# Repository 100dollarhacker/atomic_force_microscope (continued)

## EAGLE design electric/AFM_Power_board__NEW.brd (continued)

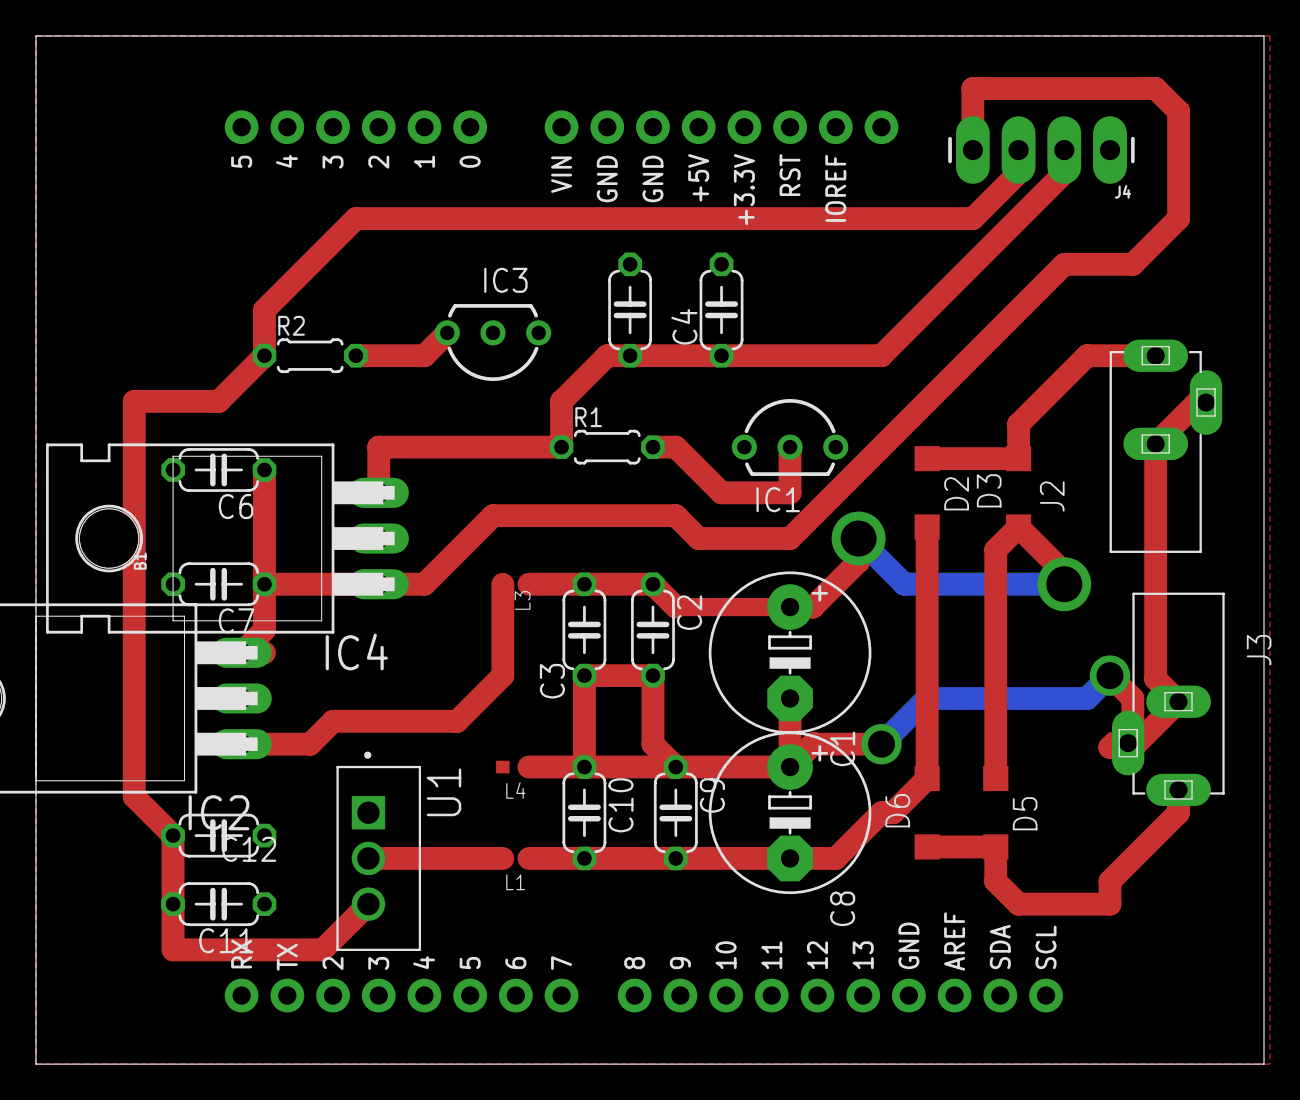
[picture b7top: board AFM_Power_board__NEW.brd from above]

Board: 2 copper layers, 68.2 x 57.1 mm, 30 parts (0 on the bottom side), 13 nets.

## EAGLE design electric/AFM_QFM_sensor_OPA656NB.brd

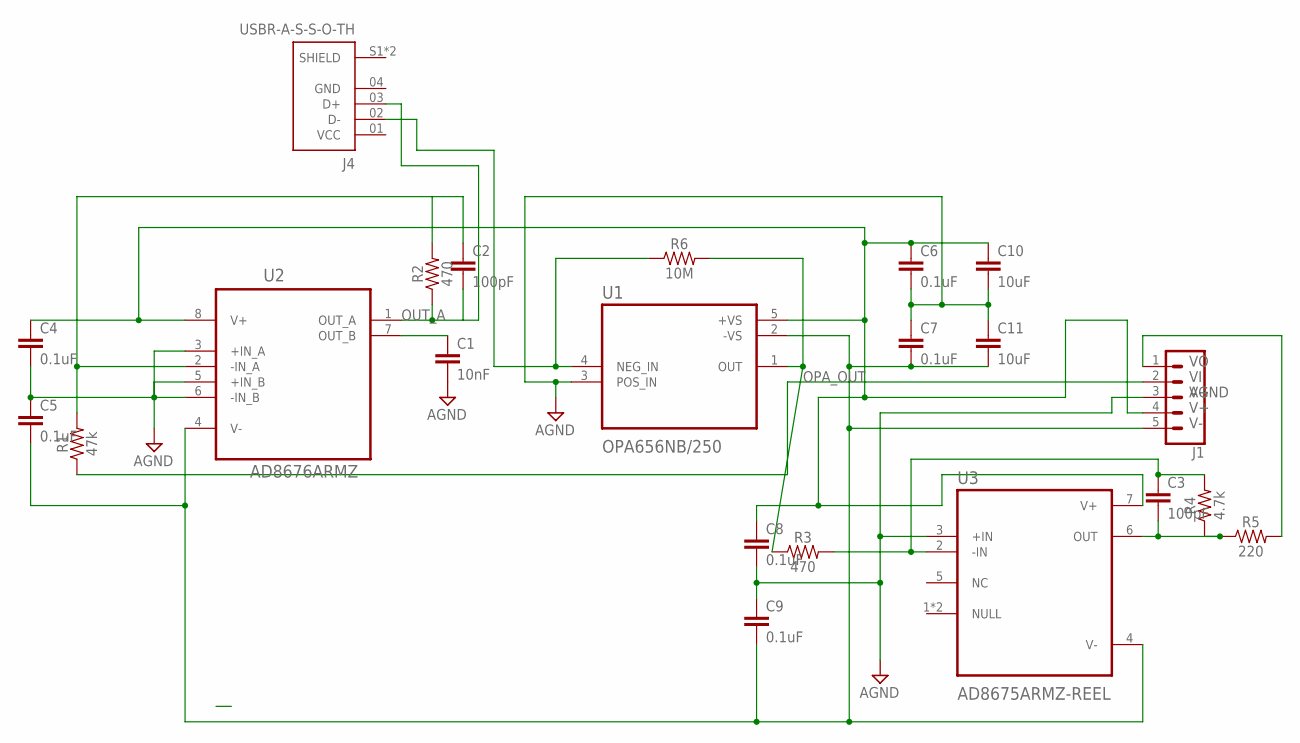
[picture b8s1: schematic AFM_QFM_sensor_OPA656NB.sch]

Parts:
C1: 10nF; 0603
C2, C3: 100pF; 0603
C4, C5, C6, C7, C8, C9: 0.1uF; 0603
C10, C11: 10uF; 0805
J1: CONN_05PTH_LONGPADS; 1X05_LONGPADS
J4: USBR-A-S-S-O-TH; SAMTEC_USBR-A-S-S-O-TH
R1: 47k; 0603
R2, R3: 470; 0603
R4: 4.7k; 0603
R5: 220; 0603
R6: 10M; 0603
U1: OPA656NB/250; SOT95P280X145-5N
U2: AD8676ARMZ; SOP65P490X110-8N
U3: AD8675ARMZ-REEL; SOP65P490X110-8N

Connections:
AGND: C1.2, C4.2, C5.1, C6.2, C7.1, C8.2, C9.1, C10.2, C11.1, J1.3, U1.3 (POS_IN), U2.3 (+IN_A), U2.5 (+IN_B), U2.6 (-IN_B), U3.3 (+IN)
GND: J4.04 (GND)
unnamed: J4.02 (D-), R6.1, U1.4 (NEG_IN)
unnamed: C1.1, U2.7 (OUT_B)
unnamed: C2.1, R1.2, R2.2, U2.2 (-IN_A)
unnamed: C3.2, R4.1, R5.1, U3.6 (OUT)
OPA_OUT: C3.1, R3.1, R3.2, R4.2, R6.2, U1.1 (OUT), U3.2 (-IN)
OUT_A: C2.2, J4.03 (D+), R2.1, U2.1 (OUT_A)
V+: C4.1, C6.1, C8.1, C10.1, J1.4, U1.5 (+VS), U2.8 (V+), U3.7 (V+)
V-: C5.2, C7.2, C9.2, C11.2, J1.5, U1.2 (-VS), U2.4 (V-), U3.4 (V-)
VCC: J4.01 (VCC)
VI: J1.2, R1.1
VO: J1.1, R5.2

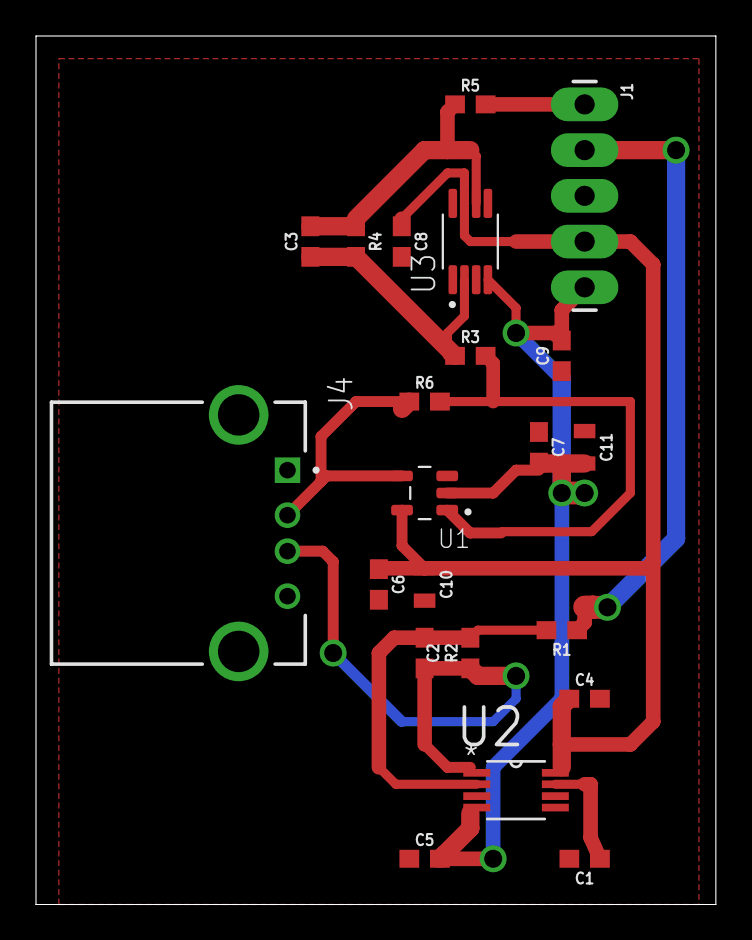
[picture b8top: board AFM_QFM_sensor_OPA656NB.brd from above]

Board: 2 copper layers, 37.8 x 48.2 mm, 22 parts (0 on the bottom side), 11 nets.

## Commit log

2023-07-18 Files needed to create nono sized tip
2023-07-21 old OpenAFM schematics
2023-08-17 This is a very basic but working DAC
2023-10-08 POC fine mechanical and coarse mechanical
2023-10-12 Nano probe holder
2024-03-05 initial electoring circuits added
2024-04-05 allboards
2024-04-06 movied power lines to right position
2024-05-19 Charge pump with his own power source
2024-07-04 new firmware
2024-07-05 UI and simple main components
2024-07-06 more components
2024-07-07 Connected AD5696 conroll
2024-07-07 swing in Z working
2024-07-07 some last minute fixs
2024-07-08 ad9833 controller
2024-07-08 Added frequency sensor
2024-07-09 working my code
2024-08-04 afm sensor holder with bolts holders
2024-08-04 upper parth with bolt holder
2024-08-17 new functions and samples
2024-11-04 newer electroincs
2024-12-21 use long as int is 16bit
2024-12-21 simplfy freq
2024-12-22 minor fix
2024-12-30 software change, try to run with one frequncy
2024-12-30 BOM - Bill Of Materials for all the boards
2024-12-30 Updated to boards. Changes reflects fixes needed to PCBWay boards
2024-12-30 removed unused files
2024-12-30 removed old
2024-12-30 remove old files
2025-02-27 different kind of scans
2025-02-27 first data visualized
2025-03-07 added ringing functionality to check piezos and added micropositioner controller
2025-03-19 simple gui added, mainly buttons that doesn't do a thing and a plot with fake data
2025-03-19 colorbar added
2025-03-20 frequency controll added
2025-03-21 serial connected, getting/setting freq done
2025-03-21 send the min freuency
2025-03-21 added scan thread and other buttons
2025-03-21 added lr and rl scans
2025-03-22 most of the buttons are functional, not tested on real device yet
2025-03-23 made most of function to work with GUI
2025-03-23 make GUI work with firmaware mostly
2025-03-24 get the data
2025-03-24 up/down firmware
2025-03-26 make it run faster
2025-03-26 different maginfications
2025-05-20 make serail a thread
2025-05-20 range with number
2025-05-20 made posible to run scan prallel to down/up
2025-05-20 demo flag added
2025-05-23 adding ability to trace surface
2025-05-23 still debuging
2025-05-23 some silly debugs
2025-05-24 fix merge
2025-05-25 strange build behavior
2025-05-26 fixed scanxlr
2025-05-26 scanning looks good
2025-05-27 moving to more efficient serial reader implementation
2025-05-27 simiplified serial communications
2025-05-27 working now
2025-09-25 make range work again
2025-09-26 wrong merge
2025-09-26 frequency are not limited by 32768
2025-09-26 removing tiny bug which made me a lot of troubles
2025-09-26 typo
2025-10-04 tested version of approach
2025-10-10 remove debugs so scannig could work nwo
2025-10-11 name changed and fixed direction of convergence
2025-10-11 fix another issue now it's able to scan
2025-10-11 fix default step size to 1 and try linear normalization
2025-10-11 reduced step size to 10 instead of 100
2025-10-11 let steps size come from higher level
2025-10-11 change color bar to dynamic instead of 0-2000
2025-10-13 added option to control nano step size and it's working!
2025-10-20 fixed broken python
2025-10-20 add 500ms delay to x-scanning movement otherwise all data in X-axis is the same and disable 32K restriction
2025-10-21 removed logs and made high to be as high number and low low number
2025-10-22 fixing few bugs must be checed
2025-10-24 The image already reverted
2025-10-24 Make an image from CSV file
2025-10-24 example images
2025-11-05 basic pseudo DAC added and working
2025-11-05 software bug fixed
2025-11-10 some fixes for stabilization
2025-11-10 split to afm and stm python files
2025-12-16 make stm slower
